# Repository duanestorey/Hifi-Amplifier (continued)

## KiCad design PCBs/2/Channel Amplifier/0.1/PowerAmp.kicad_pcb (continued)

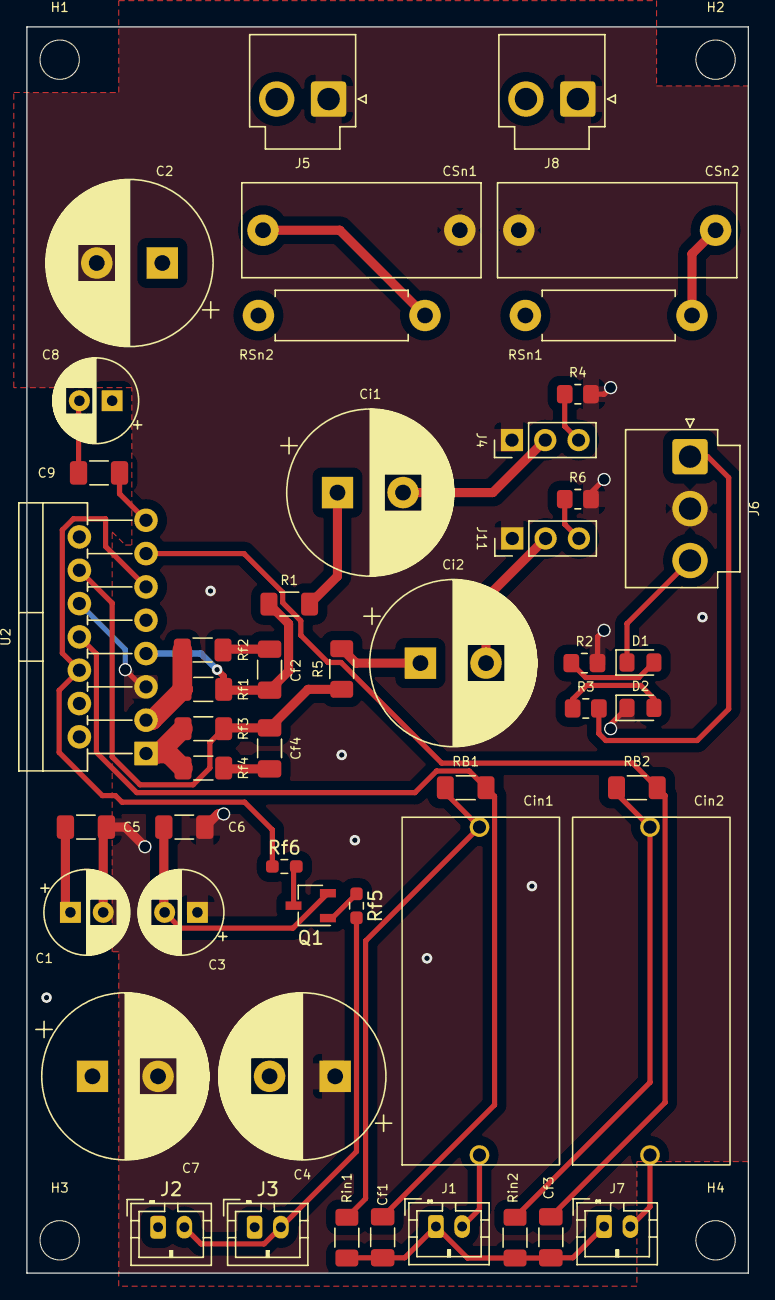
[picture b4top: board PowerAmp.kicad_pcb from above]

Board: 4 copper layers, 55.0 x 95.0 mm, 54 parts (0 on the bottom side), 30 nets.

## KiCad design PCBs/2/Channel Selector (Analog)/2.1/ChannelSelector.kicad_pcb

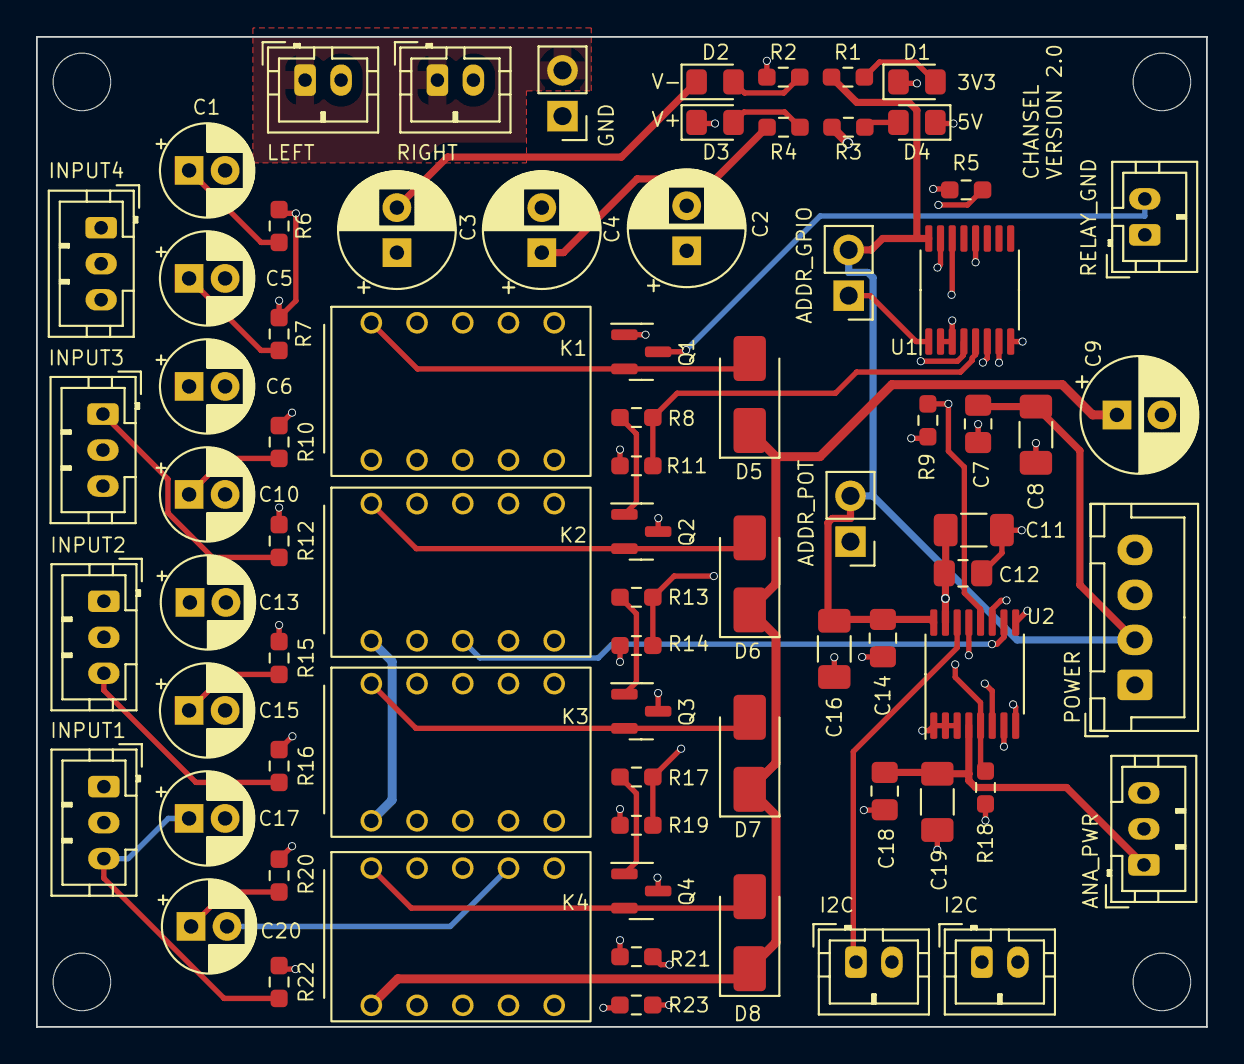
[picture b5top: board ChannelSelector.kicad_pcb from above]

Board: 4 copper layers, 65.0 x 55.0 mm, 79 parts (0 on the bottom side), 49 nets.

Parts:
C1, C5, C6, C10, C13, C15, C17, C20: 10u; CP_Radial_D5.0mm_P2.00mm
C2, C3, C4, C9: 470u; CP_Radial_D6.3mm_P2.50mm
C7, C12, C14, C18: 0.1U; C_0805_2012Metric_Pad1.18x1.45mm_HandSolder
C8, C16: 10U; C_1206_3216Metric_Pad1.33x1.80mm_HandSolder
C11, C19: 47U; C_1206_3216Metric_Pad1.33x1.80mm_HandSolder
D1, D3: YELLOW; LED_0805_2012Metric_Pad1.15x1.40mm_HandSolder
D2, D4: BLUE; LED_0805_2012Metric_Pad1.15x1.40mm_HandSolder
D5, D6, D7, D8: 1N4001; D_SMA
H1, H2, H3, H4: MountingHole; MountingHole_3.2mm_M3
J1, J2, J4: Conn_01x02_Pin; JST_PH_B2B-PH-K_1x02_P2.00mm_Vertical
J3: Conn_01x02_Male; PinHeader_1x02_P2.54mm_Vertical
J5, J7, J10, J11: Conn_01x03_Pin; JST_PH_B3B-PH-K_1x03_P2.00mm_Vertical
J6, J8: Conn_01x02_Pin; PinHeader_1x02_P2.54mm_Vertical
J9: Conn_01x04_Pin; JST_XH_B4B-XH-A_1x04_P2.50mm_Vertical
J12: Conn_01x03_Male; JST_PH_B3B-PH-K_1x03_P2.00mm_Vertical
J13, J14: Conn_01x02_Male; JST_PH_B2B-PH-K_1x02_P2.00mm_Vertical
K1, K2, K3, K4: EA2-5NU; KEMET EA2
Q1, Q2, Q3, Q4: BC859; SOT-23
R1: 430R; R_0603_1608Metric_Pad0.98x0.95mm_HandSolder
R2: 1k; R_0603_1608Metric_Pad0.98x0.95mm_HandSolder
R3: 670R; R_0603_1608Metric_Pad0.98x0.95mm_HandSolder
R4: 1.25k; R_0603_1608Metric_Pad0.98x0.95mm_HandSolder
R5, R9, R11, R14, R18, R19, R23: 4.7K; R_0603_1608Metric_Pad0.98x0.95mm_HandSolder
R6, R7, R10, R12, R15, R16, R20, R22: 50k; R_0603_1608Metric_Pad0.98x0.95mm_HandSolder
R8, R13, R17, R21: 1K; R_0603_1608Metric_Pad0.98x0.95mm_HandSolder
U1: TCA9554PW; TSSOP-16_4.4x5mm_P0.65mm
U2: DS1882E; TSSOP-16_4.4x5mm_P0.65mm

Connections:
3V3: C2.1, C7.1, C8.1, C14.1, C16.1, J6.2, J8.2, J9.2, R1.1, U1.16 (VDD), U2.16 (VDD)
5V: C9.1, D5.1 (K), D6.1 (K), D7.1 (K), D8.1 (K), J9.4, K1.1, K2.1, K3.1, K4.1, R3.1
A0: J8.1, R18.1, U2.5 (A0)
A0_2: J6.1, R5.1, U1.1 (A0)
AGND: C11.2, C12.2, C18.2, C19.2, D3.1 (K), J3.1, J5.2, J7.2, J10.2, J11.2, J12.2, R2.1, R6.1, R7.1, R10.1, R12.1, R15.1, R16.1, R20.1, R22.1, U2.7 (L0), U2.9 (L1)
CE: R9.2, U1.12 (P7), U2.12 (~CE)
FL_AIN: K1.9, K2.9, K3.9, K4.9, U2.8 (H0)
FL_AV: J1.2, U2.6 (W0)
FR_AIN: K1.4, K2.4, K3.4, K4.4, U2.10 (H1)
FR_AV: J2.2, U2.11 (W1)
GND: C2.2, C3.1, C4.2, C7.2, C8.2, C9.2, C14.2, C16.2, D1.1 (K), D4.1 (K), J4.1, J9.1, J9.3, R5.2, R9.1, R11.1, R14.1, R18.2, R19.1, R23.1, U1.2 (A1), U1.3 (A2), U1.8 (GND), U2.1 (GND), U2.2 (A2), U2.3 (A1)
GND_OUT: J1.1, J2.1, J3.2
unnamed: D1.2 (A), R1.2
unnamed: D2.2 (A), R2.2
unnamed: D3.2 (A), R4.2
unnamed: D4.2 (A), R3.2
unnamed: D5.2 (A), K1.12, Q1.2 (E)
unnamed: D6.2 (A), K2.12, Q2.2 (E)
unnamed: D7.2 (A), K3.12, Q3.2 (E)
unnamed: D8.2 (A), K4.12, Q4.2 (E)
unnamed: C1.1, J5.1, R6.2
unnamed: C5.1, J5.3, R7.2
unnamed: C6.1, J7.1, R12.2
unnamed: C10.1, J7.3, R10.2
unnamed: C15.1, J10.1, R15.2
unnamed: C13.1, J10.3, R16.2
unnamed: C20.1, J11.1, R20.2
unnamed: C17.1, J11.3, R22.2
unnamed: Q1.1 (B), R21.2
unnamed: Q2.1 (B), R8.2
unnamed: Q3.1 (B), R13.2
unnamed: Q4.1 (B), R17.2
RCA1: R17.1, R19.2, U1.7 (P3)
RCA1_L: C20.2, K4.8
RCA1_R: C17.2, K4.5
RCA2: R13.1, R14.2, U1.6 (P2)
RCA2_L: C15.2, K3.8
RCA2_R: C13.2, K3.5
RCA3: R8.1, R11.2, U1.5 (P1)
RCA3_L: C6.2, K2.8
RCA3_R: C10.2, K2.5
RCA4: R21.1, R23.2, U1.4 (P0)
RCA4_L: C1.2, K1.8
RCA4_R: C5.2, K1.5
REL_GND: J4.2, Q1.3 (C), Q2.3 (C), Q3.3 (C), Q4.3 (C)
SCL: J13.1, J14.1, U1.14 (SCL), U2.14 (SCL)
SDA: J13.2, J14.2, U1.15 (SDA), U2.13 (SDA)
V+: C4.1, C11.1, C12.1, J12.3, R4.1, U2.15 (VCC)
V-: C3.2, C18.1, C19.1, D2.1 (K), J12.1, U2.4 (V-)

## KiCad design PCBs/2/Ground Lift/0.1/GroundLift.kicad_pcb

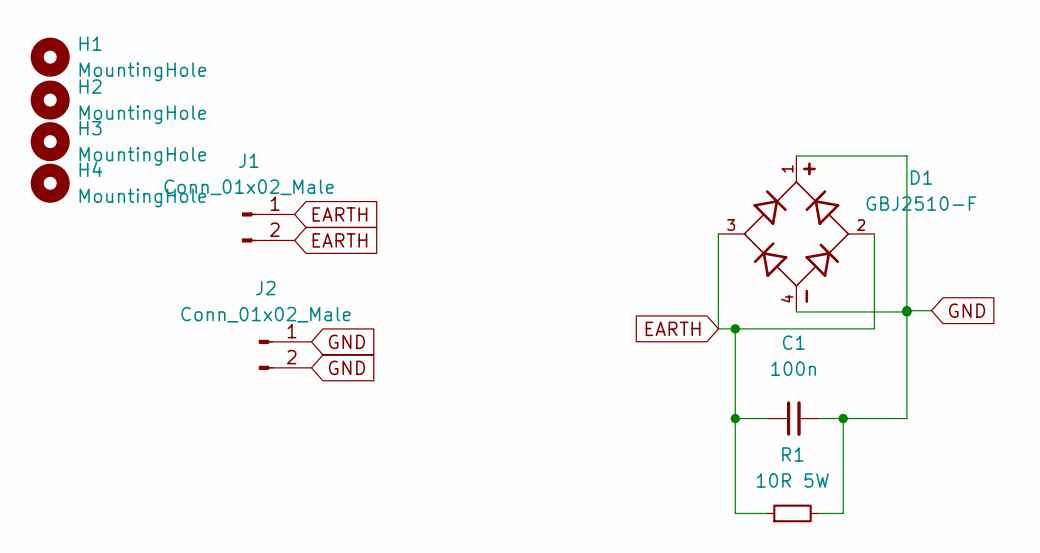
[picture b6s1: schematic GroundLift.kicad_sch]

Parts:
C1: 100n; C_Rect_L18.0mm_W5.0mm_P15.00mm_FKS3_FKP3
D1: GBJ2510-F; Diode_Bridge_19.0x19.0x6.8mm_P12.7mm
H1, H2, H3, H4: MountingHole; MountingHole_3.2mm_M3
J1, J2: Conn_01x02_Male; JST_VH_B2P-VH-B_1x02_P3.96mm_Vertical
R1: 10R 5W; R_Axial_Power_L25.0mm_W9.0mm_P27.94mm

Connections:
EARTH: C1.1, D1.2, D1.3, J1.1, J1.2, R1.1
GND: C1.2, D1.1, D1.4, J2.1, J2.2, R1.2

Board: 2 copper layers, 9 parts (0 on the bottom side), 2 nets, no tracks yet.

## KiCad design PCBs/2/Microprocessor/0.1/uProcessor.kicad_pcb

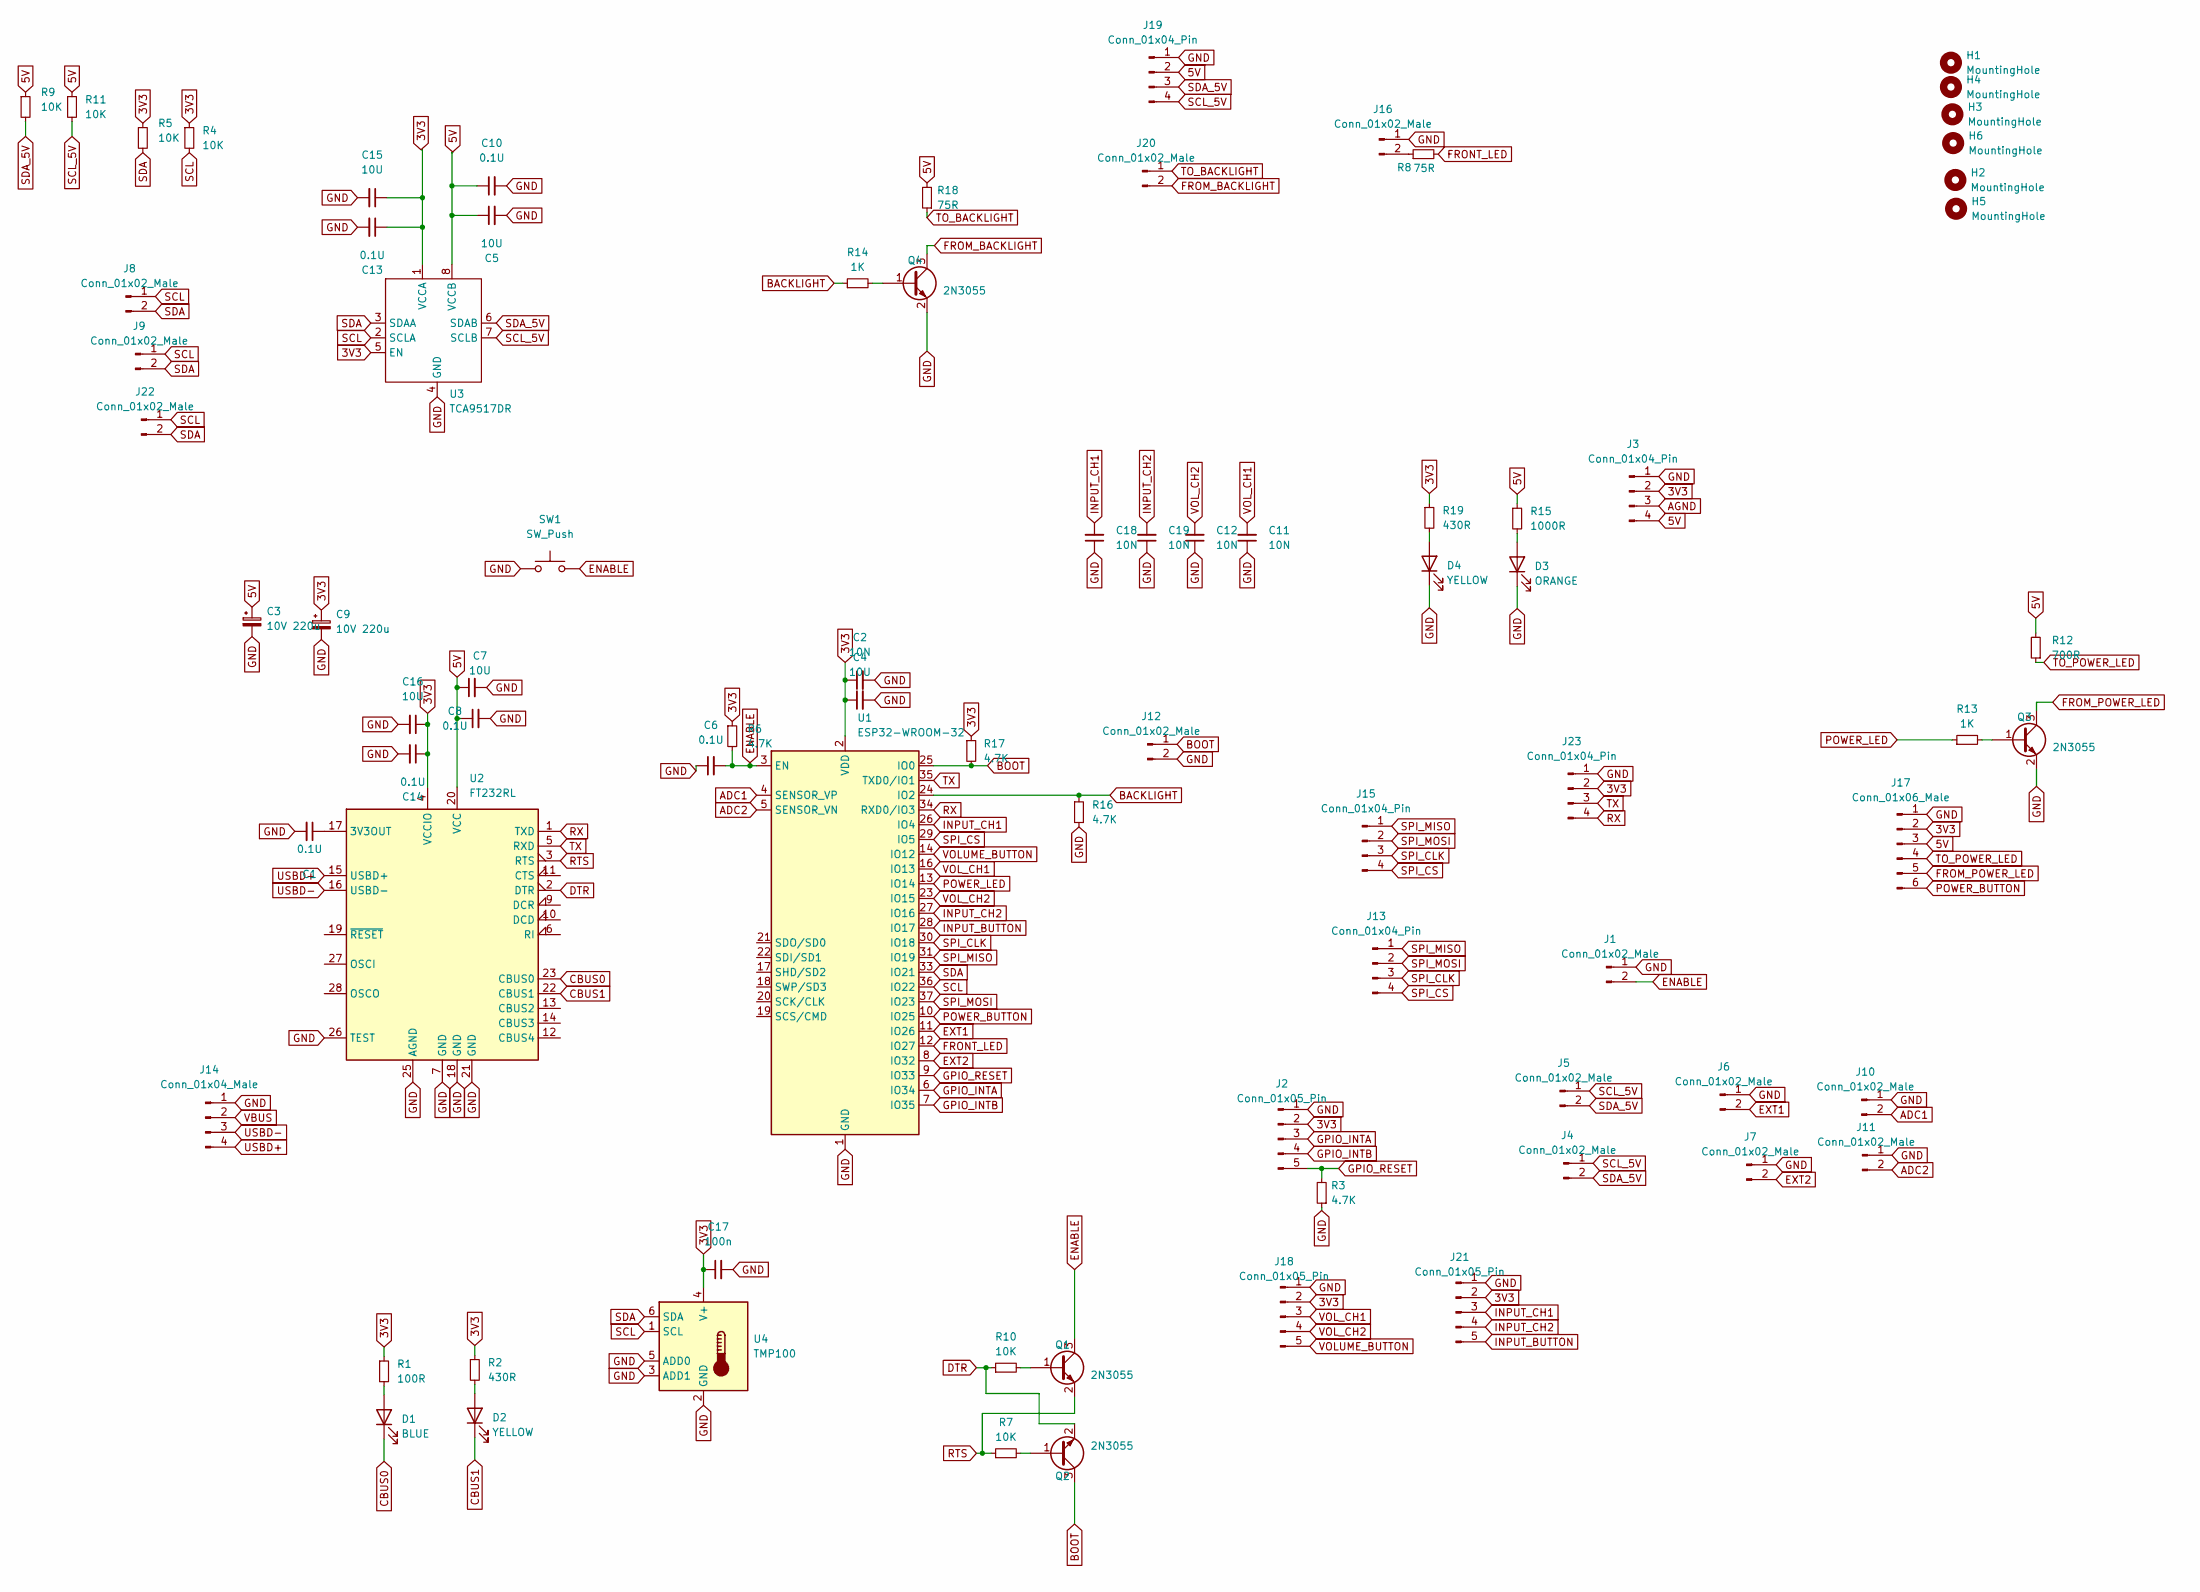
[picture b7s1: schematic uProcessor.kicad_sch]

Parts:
C1, C6, C8, C10, C13, C14: 0.1U; C_0805_2012Metric_Pad1.18x1.45mm_HandSolder
C2: 10N; C_0805_2012Metric_Pad1.18x1.45mm_HandSolder
C3, C9: 10V 220u; CP_Radial_D6.3mm_P2.50mm
C4, C5, C7, C15, C16: 10U; C_1206_3216Metric_Pad1.33x1.80mm_HandSolder
C11, C12, C18, C19: 10N; C_0603_1608Metric_Pad1.08x0.95mm_HandSolder
C17: 100n; C_0805_2012Metric_Pad1.18x1.45mm_HandSolder
D1: BLUE; LED_0805_2012Metric_Pad1.15x1.40mm_HandSolder; LCSC XL-1608UBC-04
D2: YELLOW; LED_0805_2012Metric_Pad1.15x1.40mm_HandSolder; LCSC XL-1608UBC-04
D3: ORANGE; LED_0805_2012Metric_Pad1.15x1.40mm_HandSolder; LCSC XL-1608UBC-04
D4: YELLOW; LED_0805_2012Metric_Pad1.15x1.40mm_HandSolder; LCSC NCD0603R1
H1, H2, H3, H4, H5, H6: MountingHole; MountingHole_3.2mm_M3
J1, J4, J5, J6, J7, J8, J9, J10, J11, J16, J20, J22: Conn_01x02_Male; JST_PH_B2B-PH-K_1x02_P2.00mm_Vertical
J2, J18, J21: Conn_01x05_Pin; JST_PH_B5B-PH-K_1x05_P2.00mm_Vertical
J3, J13, J19: Conn_01x04_Pin; JST_PH_B4B-PH-K_1x04_P2.00mm_Vertical
J12: Conn_01x02_Male; PinHeader_1x02_P2.54mm_Vertical
J14: Conn_01x04_Male; JST_PH_B4B-PH-K_1x04_P2.00mm_Vertical
J15, J23: Conn_01x04_Pin; PinHeader_1x04_P2.54mm_Vertical
J17: Conn_01x06_Male; JST_PH_B6B-PH-K_1x06_P2.00mm_Vertical
Q1, Q2, Q3, Q4: 2N3055; TSOT-23
R1: 100R; R_0603_1608Metric_Pad0.98x0.95mm_HandSolder
R2, R19: 430R; R_0603_1608Metric_Pad0.98x0.95mm_HandSolder
R3, R6, R16, R17: 4.7K; R_0603_1608Metric_Pad0.98x0.95mm_HandSolder
R4, R5, R7, R9, R10, R11: 10K; R_0603_1608Metric_Pad0.98x0.95mm_HandSolder
R8, R18: 75R; R_0603_1608Metric_Pad0.98x0.95mm_HandSolder
R12: 700R; R_0603_1608Metric_Pad0.98x0.95mm_HandSolder
R13, R14: 1K; R_0603_1608Metric_Pad0.98x0.95mm_HandSolder
R15: 1000R; R_0603_1608Metric_Pad0.98x0.95mm_HandSolder
SW1: SW_Push; Button Aliexpress 4x4
U1: ESP32-WROOM-32; ESP32-WROOM-32UE
U2: FT232RL; SSOP-28_5.3x10.2mm_P0.65mm
U3: TCA9517DR; SOIC-8_3.9x4.9mm_P1.27mm
U4: TMP100; SOT-23-6

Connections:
3V3: C2.1, C4.1, C9.1, C13.1, C14.1, C15.1, C16.1, C17.1, J2.2, J3.2, J17.2, J18.2, J21.2, J23.2, R1.1, R2.1, R4.1, R5.1, R6.1, R17.1, R19.1, U1.2 (VDD), U2.4 (VCCIO), U3.1 (VCCA), U3.5 (EN), U4.4 (V+)
5V: C3.1, C5.1, C7.1, C8.1, C10.1, J3.4, J17.3, J19.2, R9.1, R11.1, R12.2, R15.1, R18.2, U2.20 (VCC), U3.8 (VCCB)
ADC1: J10.2, U1.4 (SENSOR_VP)
ADC2: J11.2, U1.5 (SENSOR_VN)
AGND: J3.3
BACKLIGHT: R14.1, R16.1, U1.24 (IO2)
BOOT: J12.1, Q2.3 (C), R17.2, U1.25 (IO0)
CBUS0: D1.1 (K), U2.23 (CBUS0)
CBUS1: D2.1 (K), U2.22 (CBUS1)
DTR: Q2.2 (E), R10.1, U2.2 (DTR)
ENABLE: C6.2, J1.2, Q1.3 (C), R6.2, SW1.2, U1.3 (EN)
EXT1: J6.2, U1.11 (IO26)
EXT2: J7.2, U1.8 (IO32)
FROM_BACKLIGHT: J20.2, Q4.3 (C)
FROM_POWER_LED: J17.5, Q3.3 (C)
FRONT_LED: R8.2, U1.12 (IO27)
GND: C1.2, C2.2, C3.2, C4.2, C5.2, C6.1, C7.2, C8.2, C9.2, C10.2, C11.1, C12.1, C13.2, C14.2, C15.2, C16.2, C17.2, C18.1, C19.1, D3.1 (K), D4.1 (K), J1.1, J2.1, J3.1, J6.1, J7.1, J10.1, J11.1, J12.2, J14.1, J16.1, J17.1, J18.1, J19.1, J21.1, J23.1, Q3.2 (E), Q4.2 (E), R3.1, R16.2, SW1.1, U1.1 (GND), U1.15 (GND), U1.38 (GND), U1.39 (GND), U2.7 (GND), U2.18 (GND), U2.21 (GND), U2.25 (AGND), U2.26 (TEST), U3.4 (GND), U4.2 (GND), U4.3 (ADD1), U4.5 (ADD0)
GPIO_INTA: J2.3, U1.6 (IO34)
GPIO_INTB: J2.4, U1.7 (IO35)
GPIO_RESET: J2.5, R3.2, U1.9 (IO33)
INPUT_BUTTON: J21.5, U1.28 (IO17)
INPUT_CH1: C18.2, J21.3, U1.26 (IO4)
INPUT_CH2: C19.2, J21.4, U1.27 (IO16)
unnamed: D1.2 (A), R1.2
unnamed: D2.2 (A), R2.2
unnamed: D3.2 (A), R15.2
unnamed: D4.2 (A), R19.2
unnamed: J16.2, R8.1
unnamed: Q1.1 (B), R10.2
unnamed: Q2.1 (B), R7.2
unnamed: Q3.1 (B), R13.2
unnamed: Q4.1 (B), R14.2
unnamed: C1.1, U2.17 (3V3OUT)
POWER_BUTTON: J17.6, U1.10 (IO25)
POWER_LED: R13.1, U1.13 (IO14)
RTS: Q1.2 (E), R7.1, U2.3 (RTS)
RX: J23.4, U1.34 (RXD0/IO3), U2.1 (TXD)
SCL: J8.1, J9.1, J22.1, R4.2, U1.36 (IO22), U3.2 (SCLA), U4.1 (SCL)
SCL_5V: J4.1, J5.1, J19.4, R11.2, U3.7 (SCLB)
SDA: J8.2, J9.2, J22.2, R5.2, U1.33 (IO21), U3.3 (SDAA), U4.6 (SDA)
SDA_5V: J4.2, J5.2, J19.3, R9.2, U3.6 (SDAB)
SPI_CLK: J13.3, J15.3, U1.30 (IO18)
SPI_CS: J13.4, J15.4, U1.29 (IO5)
SPI_MISO: J13.1, J15.1, U1.31 (IO19)
SPI_MOSI: J13.2, J15.2, U1.37 (IO23)
TO_BACKLIGHT: J20.1, R18.1
TO_POWER_LED: J17.4, R12.1
TX: J23.3, U1.35 (TXD0/IO1), U2.5 (RXD)
USBD+: J14.4, U2.15 (USBD+)
USBD-: J14.3, U2.16 (USBD-)
VBUS: J14.2
VOLUME_BUTTON: J18.5, U1.14 (IO12)
VOL_CH1: C11.2, J18.3, U1.16 (IO13)
VOL_CH2: C12.2, J18.4, U1.23 (IO15)

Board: 2 copper layers, 80 parts (0 on the bottom side), 52 nets, no tracks yet.
